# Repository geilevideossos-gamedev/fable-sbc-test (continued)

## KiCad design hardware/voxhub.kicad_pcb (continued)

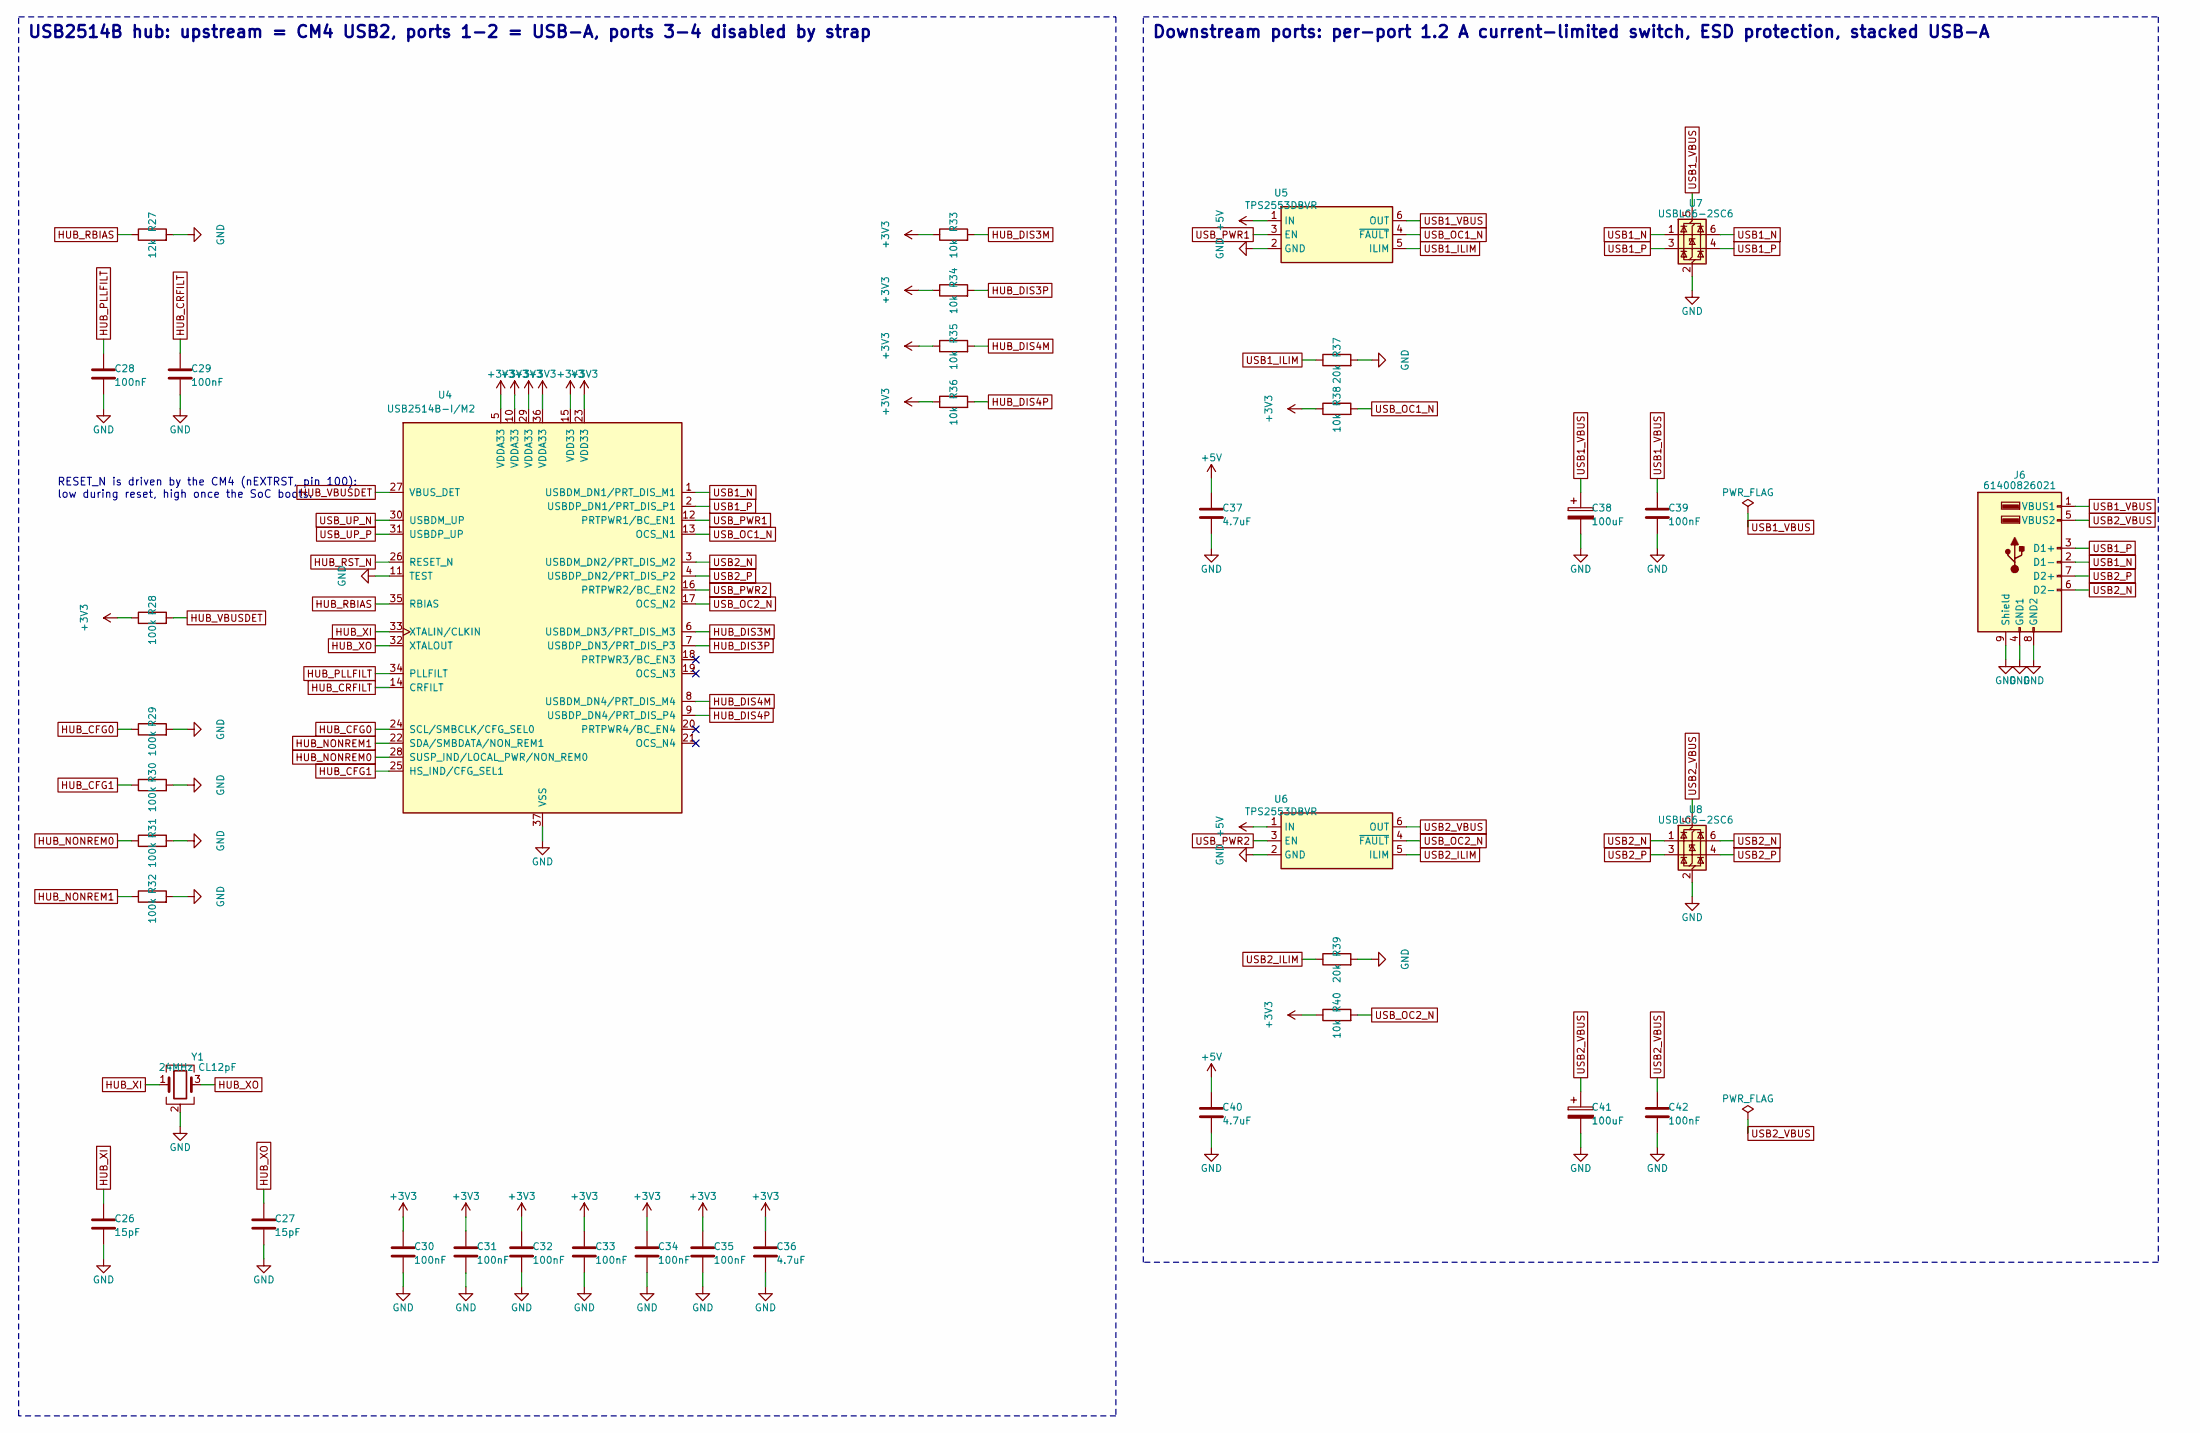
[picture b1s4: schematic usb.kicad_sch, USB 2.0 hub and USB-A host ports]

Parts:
C26, C27: 15pF; C_0402_1005Metric; MPN 0402CG150J500NT
C28, C29, C30, C31, C32, C33, C34, C35, C39, C42: 100nF; C_0402_1005Metric; MPN CL05B104KO5NNNC
C36, C37, C40: 4.7uF; C_0603_1608Metric; MPN CL10A475KA8NQNC
C38, C41: 100uF; CP_EIA-3528-21_Kemet-B; MPN T520B107M006ATE040
J6: 61400826021; USB_A_Wuerth_61400826021_Horizontal_Stacked; MPN 61400826021
R27: 12k; R_0402_1005Metric; MPN 0402WGF1202TCE
R28, R29, R30, R31, R32: 100k; R_0402_1005Metric; MPN 0402WGF1003TCE
R33, R34, R35, R36, R38, R40: 10k; R_0402_1005Metric; MPN 0402WGF1002TCE
R37, R39: 20k; R_0402_1005Metric; MPN 0402WGF2002TCE
U4: USB2514B-I/M2; QFN-36-1EP_6x6mm_P0.5mm_EP3.7x3.7mm; MPN USB2514B-I/M2
U5, U6: TPS2553DBVR; SOT-23-6; MPN TPS2553DBVR
U7, U8: USBLC6-2SC6; SOT-23-6; MPN USBLC6-2SC6
Y1: 24MHz CL12pF; Crystal_SMD_3225-4Pin_3.2x2.5mm; MPN X322524MOB4SI

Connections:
+3V3: C30.1, C31.1, C32.1, C33.1, C34.1, C35.1, C36.1, R28.1, R33.1, R34.1, R35.1, R36.1, R38.1, R40.1, U4.5 (VDDA33), U4.10 (VDDA33), U4.15 (VDD33), U4.23 (VDD33), U4.29 (VDDA33), U4.36 (VDDA33); also elsewhere on the board
+5V: C37.1, C40.1, U5.1 (IN), U6.1 (IN); also elsewhere on the board
GND: C26.2, C27.2, C28.2, C29.2, C30.2, C31.2, C32.2, C33.2, C34.2, C35.2, C36.2, C37.2, C38.2, C39.2, C40.2, C41.2, C42.2, J6.4 (GND1), J6.8 (GND2), J6.9 (Shield), R27.2, R29.2, R30.2, R31.2, R32.2, R37.2, R39.2, U4.11 (TEST), U4.37 (VSS), U5.2 (GND), U6.2 (GND), U7.2 (GND), U8.2 (GND), Y1.2 (G), Y1.4 (G); also elsewhere on the board
HUB_CFG0: R29.1, U4.24 (SCL/SMBCLK/CFG_SEL0)
HUB_CFG1: R30.1, U4.25 (HS_IND/CFG_SEL1)
HUB_CRFILT: C29.1, U4.14 (CRFILT)
HUB_DIS3M: R33.2, U4.6 (USBDM_DN3/PRT_DIS_M3)
HUB_DIS3P: R34.2, U4.7 (USBDP_DN3/PRT_DIS_P3)
HUB_DIS4M: R35.2, U4.8 (USBDM_DN4/PRT_DIS_M4)
HUB_DIS4P: R36.2, U4.9 (USBDP_DN4/PRT_DIS_P4)
HUB_NONREM0: R31.1, U4.28 (SUSP_IND/LOCAL_PWR/NON_REM0)
HUB_NONREM1: R32.1, U4.22 (SDA/SMBDATA/NON_REM1)
HUB_PLLFILT: C28.1, U4.34 (PLLFILT)
HUB_RBIAS: R27.1, U4.35 (RBIAS)
HUB_RST_N: U4.26 (RESET_N); also elsewhere on the board
HUB_VBUSDET: R28.2, U4.27 (VBUS_DET)
HUB_XI: C26.1, U4.33 (XTALIN/CLKIN), Y1.1
HUB_XO: C27.1, U4.32 (XTALOUT), Y1.3
USB1_ILIM: R37.1, U5.5 (ILIM)
USB1_N: J6.2 (D1-), U4.1 (USBDM_DN1/PRT_DIS_M1), U7.1 (I/O1), U7.6 (I/O1)
USB1_P: J6.3 (D1+), U4.2 (USBDP_DN1/PRT_DIS_P1), U7.3 (I/O2), U7.4 (I/O2)
USB1_VBUS: C38.1, C39.1, J6.1 (VBUS1), U5.6 (OUT), U7.5 (VBUS)
USB2_ILIM: R39.1, U6.5 (ILIM)
USB2_N: J6.6 (D2-), U4.3 (USBDM_DN2/PRT_DIS_M2), U8.1 (I/O1), U8.6 (I/O1)
USB2_P: J6.7 (D2+), U4.4 (USBDP_DN2/PRT_DIS_P2), U8.3 (I/O2), U8.4 (I/O2)
USB2_VBUS: C41.1, C42.1, J6.5 (VBUS2), U6.6 (OUT), U8.5 (VBUS)
USB_OC1_N: R38.2, U4.13 (OCS_N1), U5.4 (~FAULT)
USB_OC2_N: R40.2, U4.17 (OCS_N2), U6.4 (~FAULT)
USB_PWR1: U4.12 (PRTPWR1/BC_EN1), U5.3 (EN)
USB_PWR2: U4.16 (PRTPWR2/BC_EN2), U6.3 (EN)
USB_UP_N: U4.30 (USBDM_UP); also elsewhere on the board
USB_UP_P: U4.31 (USBDP_UP); also elsewhere on the board

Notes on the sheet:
USB2514B hub: upstream = CM4 USB2, ports 1-2 = USB-A, ports 3-4 disabled by strap
RESET_N is driven by the CM4 (nEXTRST, pin 100): low during reset, high once the SoC boots.
Downstream ports: per-port 1.2 A current-limited switch, ESD protection, stacked USB-A

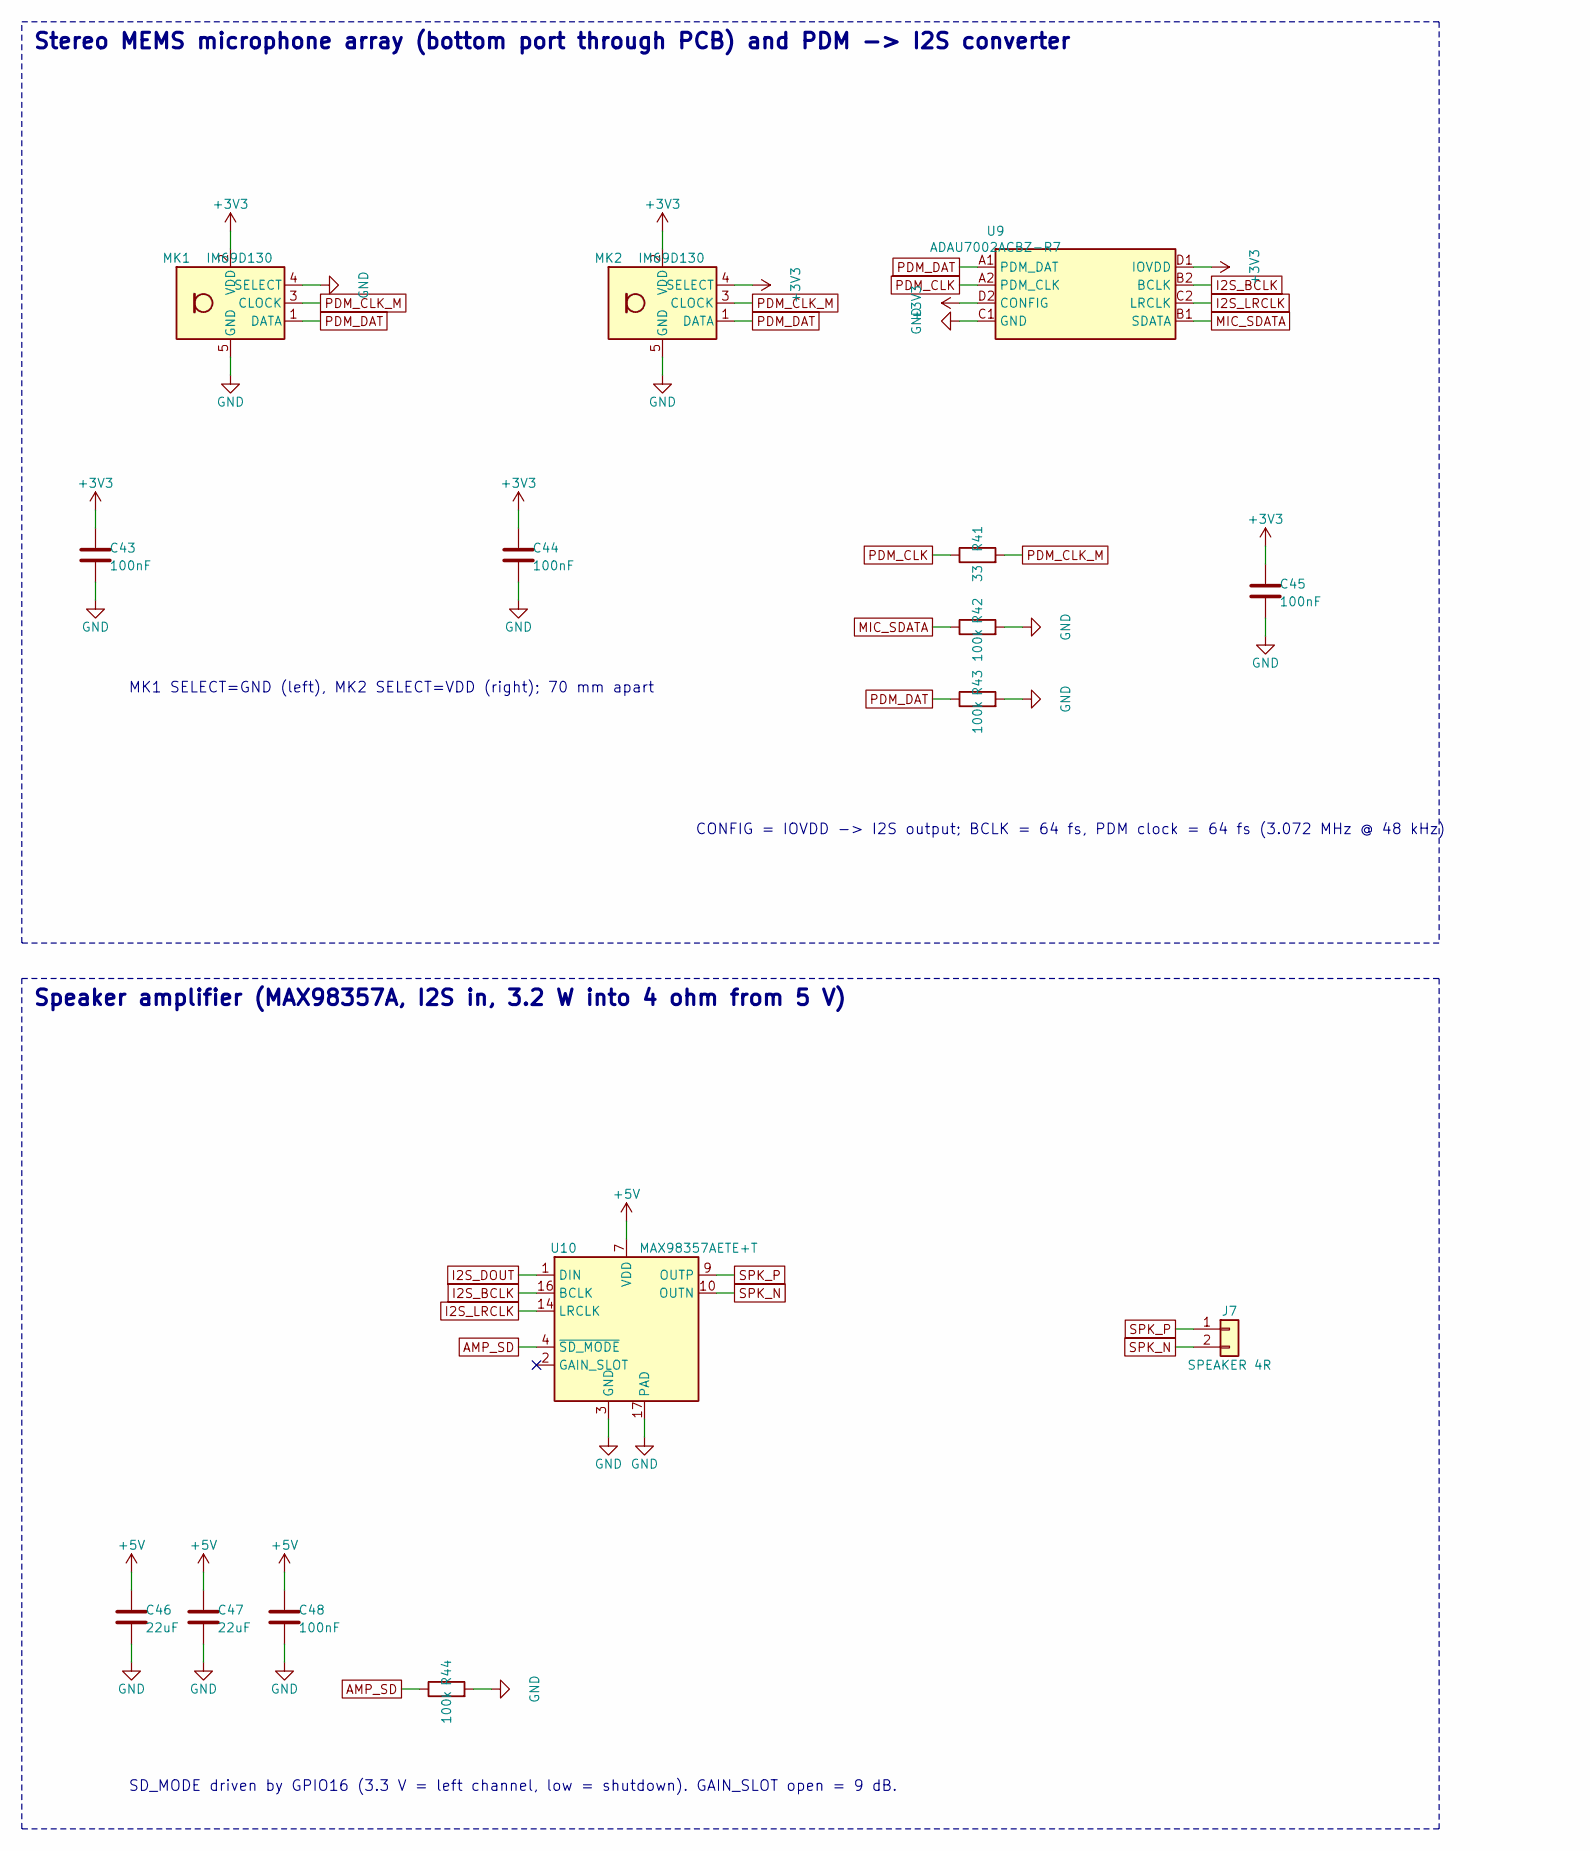
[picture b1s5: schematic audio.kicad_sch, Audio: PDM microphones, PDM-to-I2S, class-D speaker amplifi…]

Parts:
C43, C44, C45, C48: 100nF; C_0402_1005Metric; MPN CL05B104KO5NNNC
C46, C47: 22uF; C_1206_3216Metric; MPN CL31A226KAHNNNE
J7: SPEAKER 4R; JST_PH_B2B-PH-K_1x02_P2.00mm_Vertical; MPN B2B-PH-K-S(LF)(SN)
MK1, MK2: IM69D130; Infineon_PG-LLGA-5-1; MPN IM69D130V01XTSA1
R41: 33; R_0402_1005Metric; MPN 0402WGF330JTCE
R42, R43, R44: 100k; R_0402_1005Metric; MPN 0402WGF1003TCE
U9: ADAU7002ACBZ-R7; ADAU7002_WLCSP-8_0.76x1.56mm_P0.4mm; MPN ADAU7002ACBZ-R7
U10: MAX98357AETE+T; TQFN-16-1EP_3x3mm_P0.5mm_EP1.23x1.23mm; MPN MAX98357AETE+T

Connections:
+3V3: C43.1, C44.1, C45.1, MK1.2 (VDD), MK2.2 (VDD), MK2.4 (SELECT), U9.D1 (IOVDD), U9.D2 (CONFIG); also elsewhere on the board
+5V: C46.1, C47.1, C48.1, U10.7 (VDD), U10.8 (VDD); also elsewhere on the board
AMP_SD: R44.1, U10.4 (~SD_MODE); also elsewhere on the board
GND: C43.2, C44.2, C45.2, C46.2, C47.2, C48.2, MK1.4 (SELECT), MK1.5 (GND), MK2.5 (GND), R42.2, R43.2, R44.2, U9.C1 (GND), U10.3 (GND), U10.11 (GND), U10.15 (GND), U10.17 (PAD); also elsewhere on the board
I2S_BCLK: U9.B2 (BCLK), U10.16 (BCLK); also elsewhere on the board
I2S_DOUT: U10.1 (DIN); also elsewhere on the board
I2S_LRCLK: U9.C2 (LRCLK), U10.14 (LRCLK); also elsewhere on the board
MIC_SDATA: R42.1, U9.B1 (SDATA); also elsewhere on the board
PDM_CLK: R41.1, U9.A2 (PDM_CLK)
PDM_CLK_M: MK1.3 (CLOCK), MK2.3 (CLOCK), R41.2
PDM_DAT: MK1.1 (DATA), MK2.1 (DATA), R43.1, U9.A1 (PDM_DAT)
SPK_N: J7.2, U10.10 (OUTN)
SPK_P: J7.1, U10.9 (OUTP)

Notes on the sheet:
Stereo MEMS microphone array (bottom port through PCB) and PDM -> I2S converter
MK1 SELECT=GND (left), MK2 SELECT=VDD (right); 70 mm apart
CONFIG = IOVDD -> I2S output; BCLK = 64 fs, PDM clock = 64 fs (3.072 MHz @ 48 kHz)
Speaker amplifier (MAX98357A, I2S in, 3.2 W into 4 ohm from 5 V)
SD_MODE driven by GPIO16 (3.3 V = left channel, low = shutdown). GAIN_SLOT open = 9 dB.

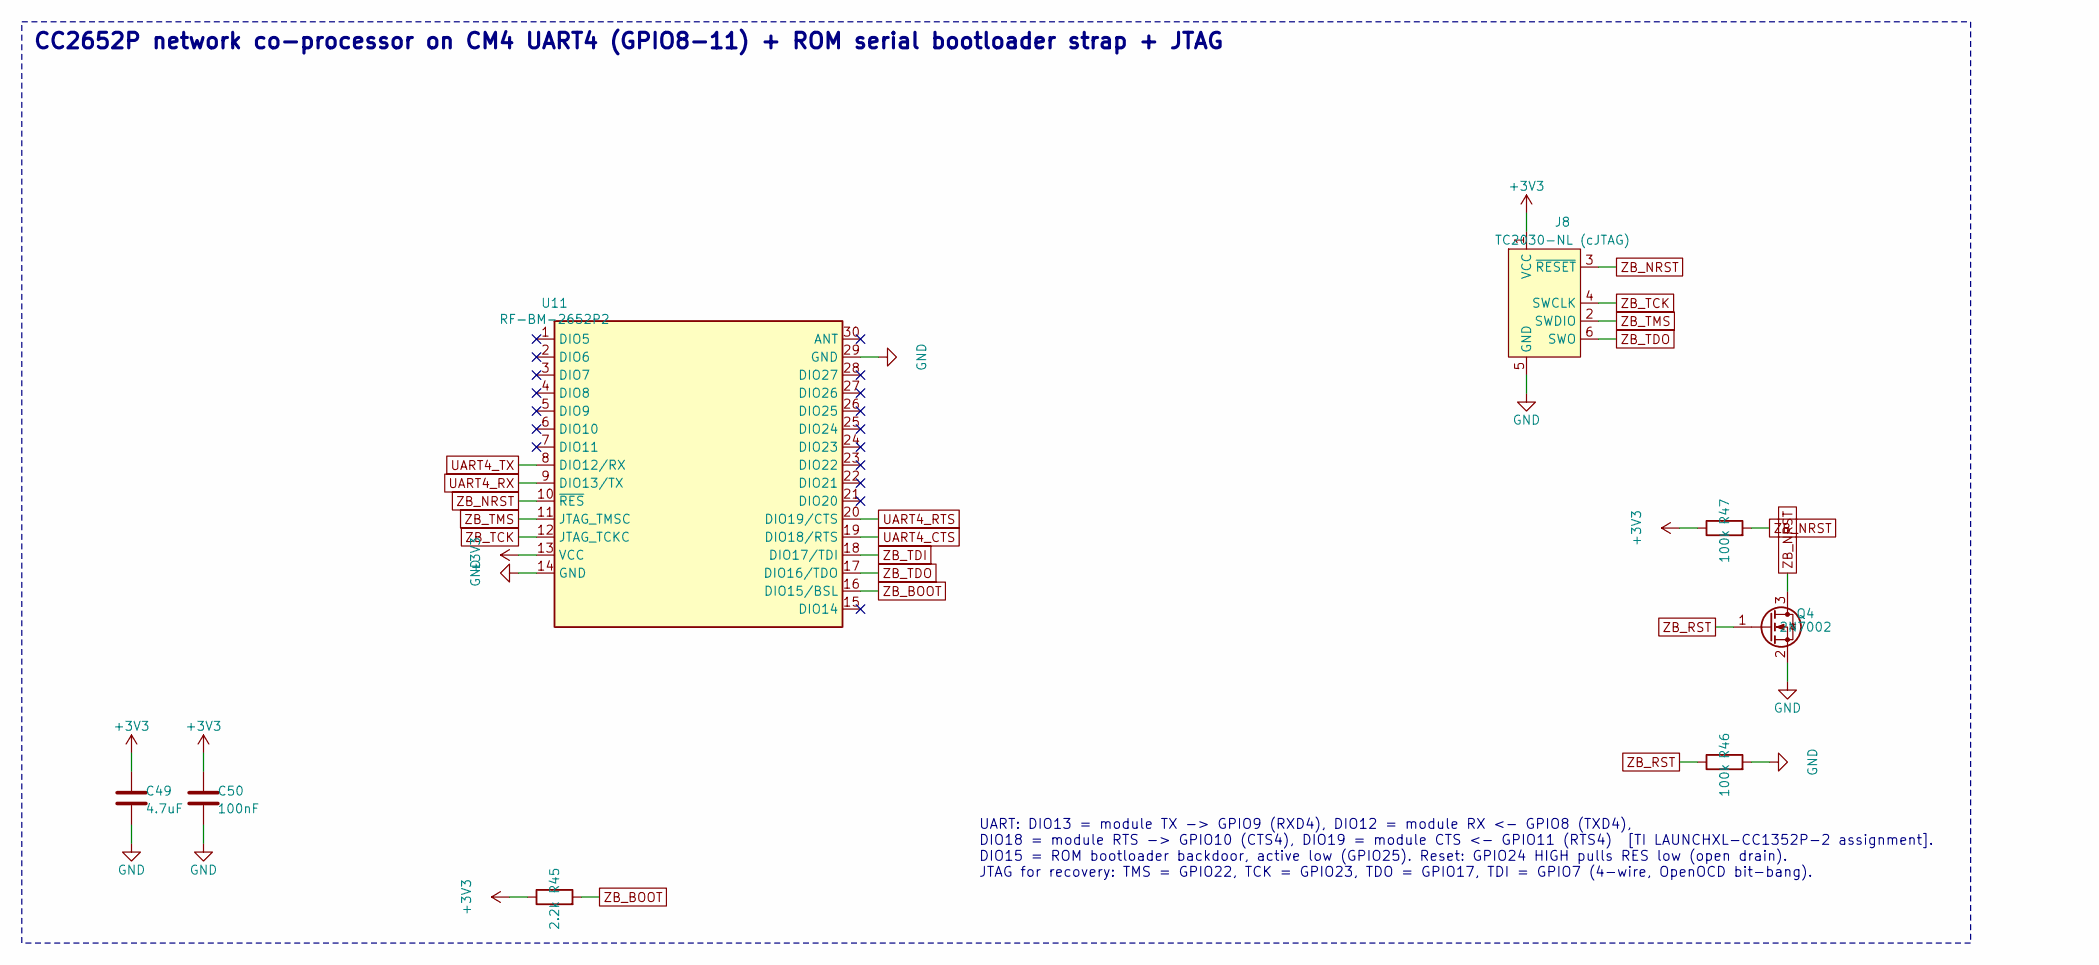
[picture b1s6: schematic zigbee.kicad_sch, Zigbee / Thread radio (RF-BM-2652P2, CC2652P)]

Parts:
C49: 4.7uF; C_0603_1608Metric; MPN CL10A475KA8NQNC
C50: 100nF; C_0402_1005Metric; MPN CL05B104KO5NNNC
J8: TC2030-NL (cJTAG); Tag-Connect_TC2030-IDC-NL_2x03_P1.27mm_Vertical; PartDescription Tag-Connect footprint (no part)
Q4: 2N7002; SOT-23; MPN 2N7002,215
R45: 2.2k; R_0402_1005Metric; MPN 0402WGF2201TCE
R46, R47: 100k; R_0402_1005Metric; MPN 0402WGF1003TCE
U11: RF-BM-2652P2; RFstar_RF-BM-2652P2; MPN RF-BM-2652P2

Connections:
+3V3: C49.1, C50.1, J8.1 (VCC), R45.1, R47.1, U11.13 (VCC); also elsewhere on the board
GND: C49.2, C50.2, J8.5 (GND), Q4.2 (S), R46.2, U11.14 (GND), U11.29 (GND); also elsewhere on the board
UART4_CTS: U11.19 (DIO18/RTS); also elsewhere on the board
UART4_RTS: U11.20 (DIO19/CTS); also elsewhere on the board
UART4_RX: U11.9 (DIO13/TX); also elsewhere on the board
UART4_TX: U11.8 (DIO12/RX); also elsewhere on the board
ZB_BOOT: R45.2, U11.16 (DIO15/BSL); also elsewhere on the board
ZB_NRST: J8.3 (~RESET), Q4.3 (D), R47.2, U11.10 (~RES)
ZB_RST: Q4.1 (G), R46.1; also elsewhere on the board
ZB_TCK: J8.4 (SWCLK), U11.12 (JTAG_TCKC); also elsewhere on the board
ZB_TDI: U11.18 (DIO17/TDI); also elsewhere on the board
ZB_TDO: J8.6 (SWO), U11.17 (DIO16/TDO); also elsewhere on the board
ZB_TMS: J8.2 (SWDIO), U11.11 (JTAG_TMSC); also elsewhere on the board

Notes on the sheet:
CC2652P network co-processor on CM4 UART4 (GPIO8-11) + ROM serial bootloader strap + JTAG
UART: DIO13 = module TX -> GPIO9 (RXD4), DIO12 = module RX <- GPIO8 (TXD4), DIO18 = module RTS -> GPIO10 (CTS4), DIO19 = module CTS <- GPIO11 (RTS4) [TI LAUNCHXL-CC1352P-2 assignment]. DIO15 = ROM bootloader backdoor, active low (GPIO25). Reset: GPIO24 HIGH pulls RES low (open drain). JTAG for reco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

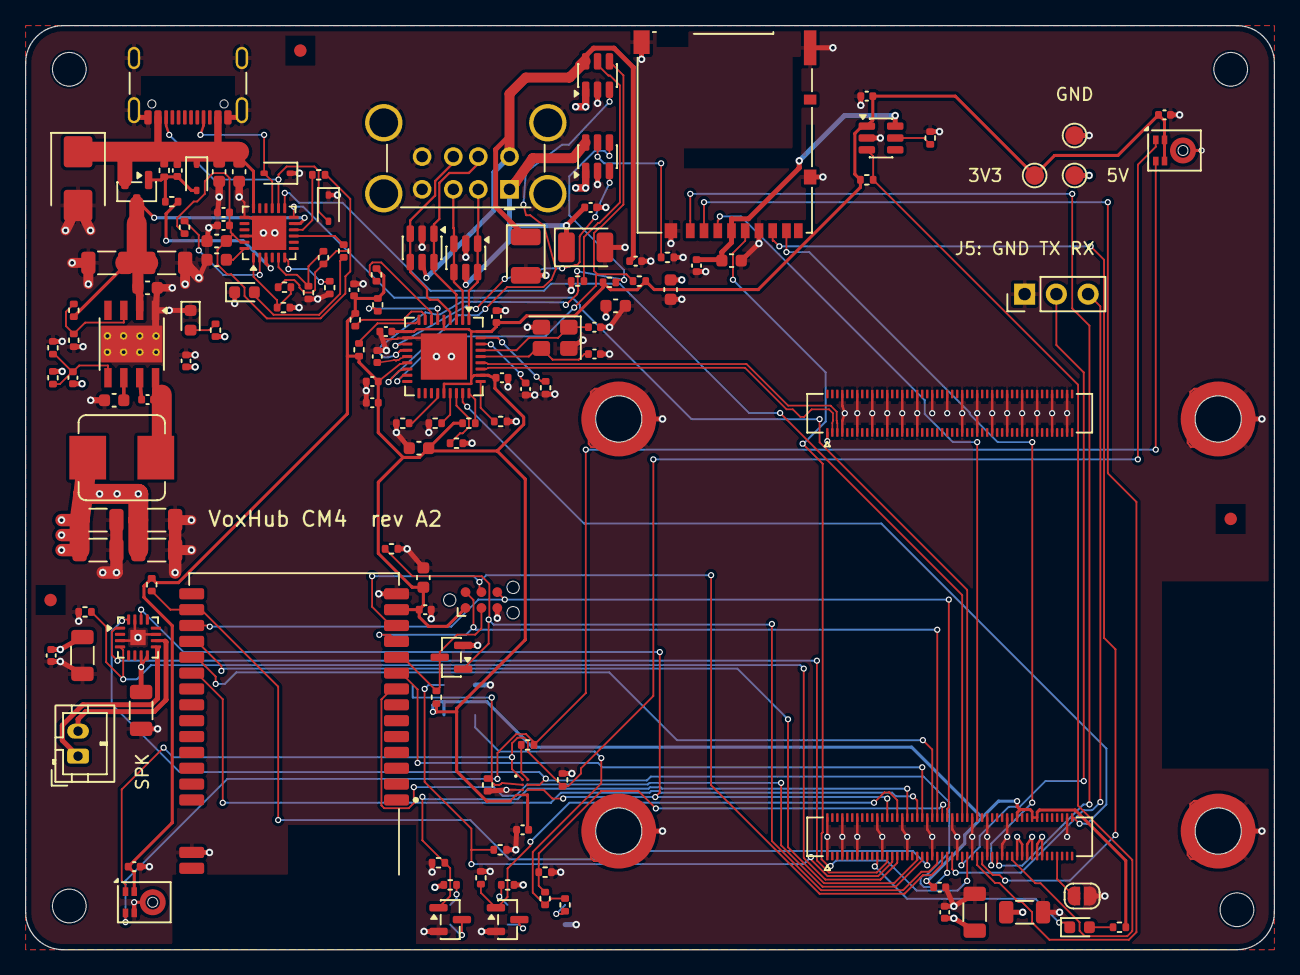
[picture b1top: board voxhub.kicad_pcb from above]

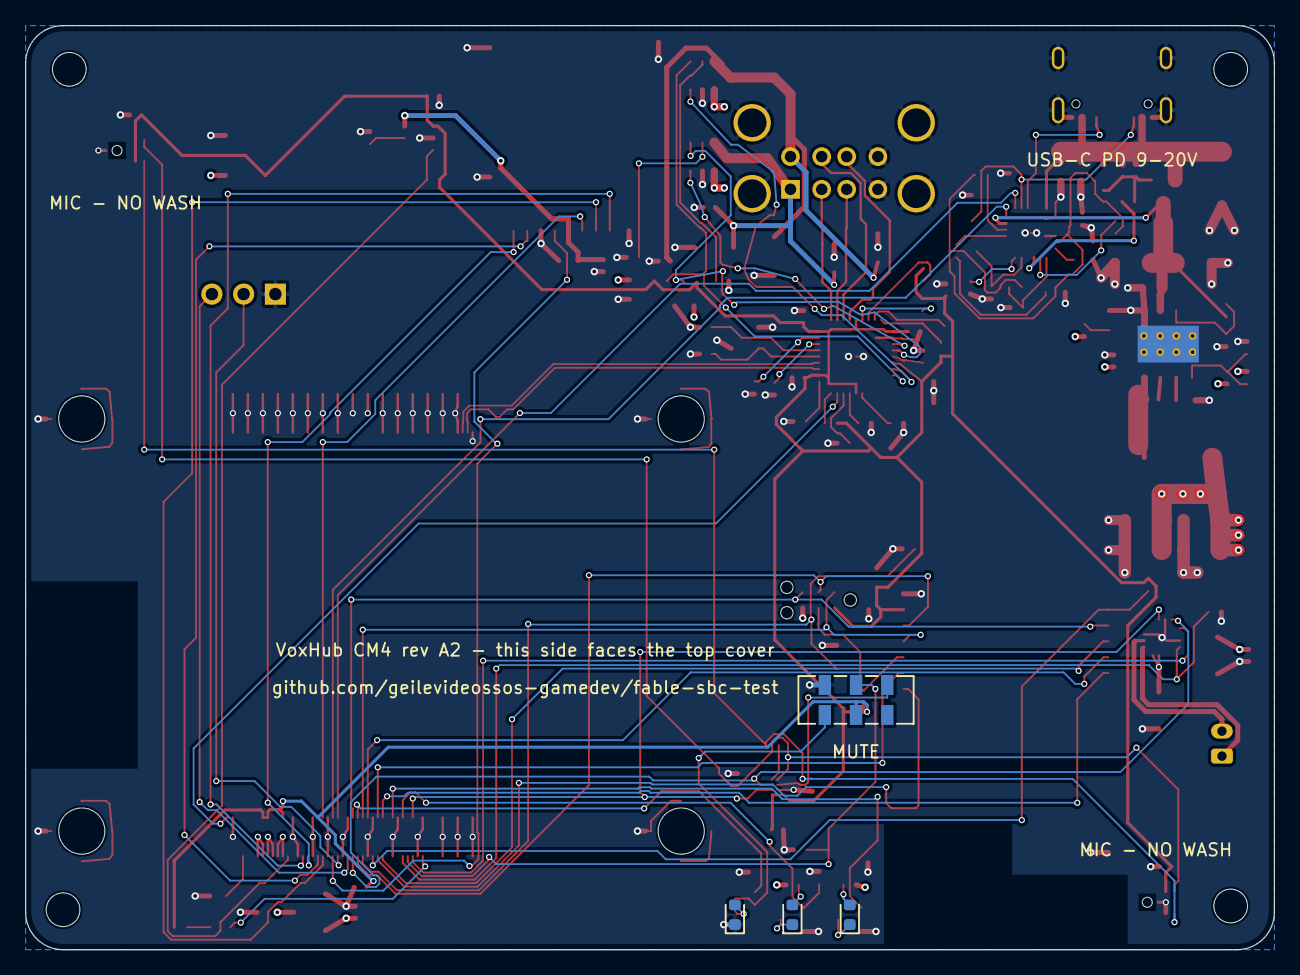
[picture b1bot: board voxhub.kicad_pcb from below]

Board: 4 copper layers, 100.0 x 74.0 mm, 150 parts (4 on the bottom side), 100 nets.

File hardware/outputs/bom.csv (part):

Item,Qty,References,Value,Description,Footprint,Manufacturer,MPN,DNP,LCSC Part #,JLCPCB type,JLCPCB stock,LCSC stock,JLCPCB USD @1,JLCPCB USD @10,JLCPCB USD @100,Ext. USD @1,Ext. USD @100,Assembly,DigiKey MPN (second source),DigiKey PN,DigiKey status,DigiKey stock,DigiKey USD @1,DigiKey USD @100,Other second sources,"Sourcing note (JLCPCB/LCSC checked 2026-11-12, DigiKey 2026-11-11)"
1,1,C1,1uF,CAP CER 1uF 50V X5R 0603,C_0603_1608Metric,Samsung Electro-Mechanics,CL10A105KB8NNNC,,C15849,Basic,13930106,1382400,0.0113,0.0113,0.0113,0.01,0.01,SMT,C1608X5R1H105K080AB,445-7468-1-ND,Active,9276,0.17,0.0579,TDK C1608X5R1H105K080AB (the A1 part),same ratings as the A1 part (50 V X5R)
2,1,C2,100nF,CAP CER 100nF 50V X7R 0603,C_0603_1608Metric,Yageo,CC0603KRX7R9BB104,,C14663,Basic,36401649,249700,0.006,0.006,0.006,0.01,0.01,SMT,C0603C104K5RACTU,399-C0603C104K5RACTUCT-ND,Active,2463252,0.14,0.046,KEMET C0603C104K5RACTU (the A1 part); any 0603 100 nF X7R 50 V,same ratings as the A1 part
3,3,C3 C5 C11,1uF,CAP CER 1uF 25V X7R 0603,C_0603_1608Metric,Samsung Electro-Mechanics,CL10B105KA8NNNC,,C29936,Extended,4509875,4284100,0.0124,0.0124,0.0097,0.04,0.03,SMT,C1608X7R1C105K080AC,445-1604-1-ND,Active,805635,0.12,0.0411,"TDK C1608X7R1C105K080AC (16 V, the A1 part), Samsung CL10B105KO8NNNC (16 V, JLCPCB C59782): 1 uF X7R 0603",25 V instead of 16 V; X7R kept on purpose (DC bias)
4,23,C4 C6 C12 C18 C19 C21 C24 C25 C28 C29 C30 C31 C32 C33 C34 C35 C39 C42 C43 C44 C45 C48 C50,100nF,CAP CER 100nF 16V X7R 0402,C_0402_1005Metric,Samsung Electro-Mechanics,CL05B104KO5NNNC,,C1525,Basic,33093790,3017800,0.0029,0.0029,0.0029,0.07,0.07,SMT,CL05B104KO5NNNC,1276-1001-1-ND,Active,10000,0.10,0.0115,any 0402 100 nF X7R >= 16 V,
5,1,C7,10nF,CAP CER 10nF 50V X7R 0402,C_0402_1005Metric,Samsung Electro-Mechanics,CL05B103KB5NNNC,,C15195,Basic,5543060,1498700,0.0037,0.0037,0.0037,0.00,0.00,SMT,CL05B103KB5NNNC,1276-1028-1-ND,Active,3769991,0.10,0.0104,any 0402 10 nF X7R 50 V,
6,2,C8 C9,10uF,CAP CER 10uF 50V X7R 1206,C_1206_3216Metric,Samsung Electro-Mechanics,CL31B106KBHNNNE,,C89632,Extended,468888,319710,0.2124,0.2124,0.1646,0.42,0.33,SMT,CL31B106KBHNNNE,1276-6767-1-ND,Active,0,0.42,0.168,TDK C3216X7R1H106KT0A0E (JLCPCB C694197),X7R as the LMR33640 data sheet requires for CIN. A1 flagged this line: 0 at DigiKey. JLCPCB has it in stock
7,1,C10,220nF,CAP CER 220nF 50V X7R 0603,C_0603_1608Metric,Murata,GRM188R71H224KAC4D,,C669503,Extended,4047,4040,0.0738,0.0738,0.0609,0.07,0.06,SMT,GRM188R71H224KAC4D,490-12546-1-ND,Active,not shown,0.15,0.052,"Samsung CL10B224KB8NNNC (JLCPCB C64705), Yageo CC0603KRX7R9BB224 (C107083): 220 nF 50 V X7R 0603",LMR33640 input bypass must be 220 nF / 50 V / X7R (data sheet)
8,1,C13,22pF,CAP CER 22pF 50V C0G 0402,C_0402_1005Metric,FH (Guangdong Fenghua),0402CG220J500NT,DNP,C1555,Basic,1490772,243900,0.0019,0.0019,0.0019,0.00,0.00,SMT,CL05C220JB5NNNC,1276-1116-1-ND,Active,372620,0.10,0.0212,any 0402 22 pF C0G 50 V,DNP
9,8,C14 C15 C16 C17 C22 C23 C46 C47,22uF,CAP CER 22uF 25V X5R 1206,C_1206_3216Metric,Samsung Electro-Mechanics,CL31A226KAHNNNE,,C12891,Basic,2517345,967820,0.1028,0.1028,0.1028,0.82,0.82,SMT,CL31A226KOHNNNE,1276-3048-1-ND,Active,0,0.44,0.1757,"Samsung CL31A226KOHNNNE (16 V, the A1 part, JLCPCB C90146)","25 V instead of 16 V, same case height (1.6 mm)"
10,5,C20 C36 C37 C40 C49,4.7uF,CAP CER 4.7uF 25V X5R 0603,C_0603_1608Metric,Samsung Electro-Mechanics,CL10A475KA8NQNC,,C69335,Extended,744008,548530,0.0427,0.0427,0.0311,0.21,0.16,SMT,C1608X5R1E475K080AC,445-9050-1-ND,Active,472029,0.25,0.0914,TDK C1608X5R1E475K080AC (the A1 part),same ratings as the A1 part (25 V X5R)
11,2,C26 C27,15pF,CAP CER 15pF 50V C0G 0402,C_0402_1005Metric,FH (Guangdong Fenghua),0402CG150J500NT,,C1548,Basic,1091876,423300,0.0026,0.0026,0.0026,0.01,0.01,SMT,,,not carried / not looked up,,,,any 0402 15 pF C0G 50 V,crystal load capacitors for CL 12 pF
12,2,C38 C41,100uF,CAP POLYMER TANT 100uF 6.3V 40mOhm 3528,CP_EIA-3528-21_Kemet-B,KEMET,T520B107M006ATE040,,C116740,Extended,2609,2609,0.5578,0.4548,0.355,1.12,0.71,SMT,T520B107M006ATE070,399-4009-1-ND,Active,19364,0.98,0.4391,"KEMET T520B107M006ATE070 (the A1 part, 70 mOhm), Vishay T55B107M6R3C0040 (JLCPCB C2158743): same footprint","replaces the 70 mOhm version: 40 mOhm, 1.8 A ripple, same case and ratings"
13,1,D1,SMBJ22A,TVS 22V 600W unidirectional SMB,D_SMB,Littelfuse,SMBJ22A,,C224015,Extended,1918,1915,0.1262,0.1262,0.1026,0.13,0.10,SMT,SMBJ22A,SMBJ22ALFCT-ND,Active,3431,0.50,0.1959,SMBJ22A from Bourns / Diodes / ST / Taiwan Semi: drop-in,LCSC C224015 is the Littelfuse listing
14,2,D2 D3,SD24C,ESD diode 24V bidirectional SOD-323,D_SOD-323,Littelfuse,SD24C-01FTG,,C207246,Extended,8806,8805,0.204,0.204,0.159,0.41,0.32,SMT,SD24C-01FTG,F6446CT-ND,Active,219,0.66,0.2598,no equal-or-better SOD-323 part found,LCSC C207246 is the Littelfuse listing
15,2,D4 D9,PD FAULT (red),"LED red 631nm 0603, 30mA",LED_0603_1608Metric,Lite-On,LTST-C191KRKT,,C125099,Extended,380670,377740,0.0192,0.0192,0.0192,0.04,0.04,SMT,150060RS75000,732-4978-1-ND,Active,269986,0.15,0.1239,Wurth 150060RS75000 (the A1 part); Hubei KENTO KT-0603R is JLCPCB Basic but rated 25 mA / 40 mW,30 mA / 75 mW / -55..+85 C: every rating of the A1 part met
16,1,D5,10V,Zener 10V 300mW SOD-323,D_SOD-323,onsemi,MM3Z10VT1G,,C39057,Extended,21866,21860,0.04,0.04,0.04,0.04,0.04,SMT,SZMM3Z10VT1G,SZMM3Z10VT1GOSCT-ND,Active,17291,0.29,0.1092,"onsemi SZMM3Z10VT1G (same die with AEC-Q101, JLCPCB C894520 - no footprint record in the JLCPCB library) or any 10 V SOD-323 zener >= 300 mW",
17,2,D6 D10,PWR (green),"LED green 570nm 0603, 30mA",LED_0603_1608Metric,Wurth Elektronik,150060VS75000,,C6848499,Extended,29587,,0.2043,0.2043,0.163,0.41,0.33,SMT,150060VS75000,732-4980-1-ND,Active,494853,0.15,0.1239,"any 0603 AlInGaP green LED, VF about 2.0 V",
18,1,D7,GREEN,"LED green 520nm 0603, 30mA (status, side B)",LED_0603_1608Metric,Hubei KENTO,KT-0603G,,C12624,Extended,292541,289550,0.0119,0.0119,0.0119,0.01,0.01,SMT,,,not carried / not looked up,,,,"any 0603 InGaN green LED >= 25 mA, -40..+85 C (VF about 2.7 V at 2 mA)",replaces the reverse-mount Wurth 156120GS75000 (0 at JLCPCB): ordinary LED on side B inside the light pipe
19,1,D8,BLUE,"LED blue 468nm 0603, 30mA (status, side B)",LED_0603_1608Metric,Hubei KENTO,KT-0603B,,C2288,Extended,82388,72150,0.0106,0.0106,0.0106,0.01,0.01,SMT,,,not carried / not looked up,,,,"any 0603 InGaN blue LED >= 25 mA, -40..+85 C",replaces the reverse-mount Wurth 156120BS75000 (not at JLCPCB): ordinary LED on side B inside the light pipe
20,4,H5 H6 H7 H8,CM4 spacer M2.5x1.5,"SMT spacer M2.5 internal thread, 1.5mm",Mounting_Wuerth_WA-SMSI-M2.5_H1.5mm_9774015151,Wurth Elektronik,9774015151R,,C5353804,Extended,230,,0.5611,0.5251,0.5251,2.24,2.10,SMT,9774015151R,732-7068-1-ND,Active,109674,1.16,0.895,Sinhoo SMTSO2515CTJ (JLCPCB C2915629) needs a 4.25 mm hole and a 6.3 mm pad - not a drop-in,"230 at JLCPCB, not sold at LCSC"
21,1,J1,USB4105-GF-A,"USB-C receptacle 16-pin USB 2.0, top mount",USB_C_Receptacle_GCT_USB4105-xx-A_16P_TopMnt_Horizontal,GCT,USB4105-GF-A,,C3020560,Extended,17519,14825,1.0207,0.8277,0.6363,1.02,0.64,SMT,USB4105-GF-A,2073-USB4105-GF-ACT-ND,Active,263569,0.80,0.5745,"none verified (GCT USB4105-GF-A-120: same footprint, longer shell stakes)",
22,2,J2 J3,DF40C-100DS-0.4V(51),CONN mezzanine 100pos 0.4mm receptacle (CM4 socket),CM4_J1_DF40C-100DS,Hirose,DF40C-100DS-0.4V(51),,C597931,Extended,1052,0,0.9667,0.8277,0.6494,1.93,1.30,SMT,DF40C-100DS-0.4V(51),H11615CT-ND,Active,164626,2.39,1.7271,"Hirose DF40HC(3.0)-100DS-0.4V(51): same land pattern, 3.0 mm stack (needs 3 mm spacers)",
23,1,J4,DM3AT-SF-PEJM5,microSD push-push socket,microSD_HC_Hirose_DM3AT-SF-PEJM5,Hirose,DM3AT-SF-PEJM5,,C114218,Extended,14909,14422,1.3903,1.1646,0.8996,1.39,0.90,SMT,DM3AT-SF-PEJM5,HR1964CT-ND,Active,74836,3.55,2.5656,none drop-in (Molex 104031-0811 needs a new footprint),
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
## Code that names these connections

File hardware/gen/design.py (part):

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CM4_NAMES = """1:GND 2:GND 3:Ethernet_Pair3_P 4:Ethernet_Pair1_P 5:Ethernet_Pair3_N 6:Ethernet_Pair1_N 7:GND 8:GND
9:Ethernet_Pair2_N 10:Ethernet_Pair0_N 11:Ethernet_Pair2_P 12:Ethernet_Pair0_P 13:GND 14:GND 15:Ethernet_nLED3
16:Ethernet_SYNC_IN 17:Ethernet_nLED2 18:Ethernet_SYNC_OUT 19:Ethernet_nLED1 20:EEPROM_nWP 21:Pi_nLED_Activity
22:GND 23:GND 24:GPIO26 25:GPIO21 26:GPIO19 27:GPIO20 28:GPIO13 29:GPIO16 30:GPIO6 31:GPIO12 32:GND 33:GND 34:GPIO5
35:ID_SC 36:ID_SD 37:GPIO7 38:GPIO11 39:GPIO8 40:GPIO9 41:GPIO25 42:GND 43:GND 44:GPIO10 45:GPIO24 46:GPIO22
47:GPIO23 48:GPIO27 49:GPIO18 50:GPIO17 51:GPIO15 52:GND 53:GND 54:GPIO4 55:GPIO14 56:GPIO3 57:SD_CLK 58:GPIO2
59:GND 60:GND 61:SD_DAT3 62:SD_CMD 63:SD_DAT0 64:SD_DAT5 65:GND 66:GND 67:SD_DAT1 68:SD_DAT4 69:SD_DAT2 70:SD_DAT7
71:GND 72:SD_DAT6 73:SD_VDD_Override 74:GND 75:SD_PWR_ON 76:Reserved 77:+5V 78:GPIO_VREF 79:+5V 80:SCL0 81:+5V
82:SDA0 83:+5V 84:+3.3V_OUT 85:+5V 86:+3.3V_OUT 87:+5V 88:+1.8V_OUT 89:WL_nDisable 90:+1.8V_OUT 91:BT_nDisable
92:RUN_PG 93:nRPIBOOT 94:AnalogIP0 95:nPWR_LED 96:AnalogIP1 97:Camera_GPIO 98:GND 99:GLOBAL_EN 100:nEXTRST
101:USB_OTG_ID 102:PCIe_CLK_nREQ 103:USB2_N 104:Reserved 105:USB2_P 106:Reserved 107:GND 108:GND 109:PCIe_nRST
110:PCIe_CLK_P 111:VDAC_COMP 112:PCIe_CLK_N 113:GND 114:GND 115:CAM1_D0_N 116:PCIe_RX_P 117:CAM1_D0_P 118:PCIe_RX_N
119:GND 120:GND 121:CAM1_D1_N 122:PCIe_TX_P 123:CAM1_D1_P 124:PCIe_TX_N 125:GND 126:GND 127:CAM1_C_N 128:CAM0_D0_N
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    res(s, rled, x, 135, V5, "LED%d_A" % i)
    led(s, key, x + 20, 150, "LED%d_A" % i, "LED%d_K" % i, name, pos=(34.0 + i * 4.6, 71.2, 90, "B"))
    q = ref("Q"); s.place("2N7002", q, "2N7002", x + 5, 180, {"1": en, "2": GND, "3": "LED%d_K" % i}, footprint=PARTS["Q_N"][3], fields=F("Q_N"))
    res(s, "10k", x, 200, en, GND)   # beats the SoC's ~50k boot-time pull-up on GPIO5/6
s.place("SW_DPDT_x2", "SW1", "JS202011JCQN (MUTE)", 375, 140, {"1": "NC", "2": V33, "3": "MIC_MUTE"}, unit=1, footprint=PARTS["SW_MUTE"][3], fields=F("SW_MUTE"))
s.place("SW_DPDT_x2", "SW1", "JS202011JCQN (MUTE)", 375, 165, {"4": "MIC_SDATA", "5": "I2S_DIN", "6": GND}, unit=2, footprint=PARTS["SW_MUTE"][3], fields=F("SW_MUTE"))
res(s, "150", 370, 185, "MIC_MUTE", "MUTE_LED_A"); led(s, "LED_R", 395, 200, "MUTE_LED_A", GND, "RED (muted)", pos=(43.2, 71.2, 90, "B"))
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         "14": "I2S_LRCLK", "15": GND, "16": "I2S_BCLK", "17": GND}, fields=F("U_AMP"))
cap(s, "C_22u", 30, 245, V5); cap(s, "C_22u", 41, 245, V5); cap(s, "C_100n", 52, 245, V5); res(s, "100k", 75, 255, "AMP_SD", GND)
s.place("Conn_01x02", "J7", "SPEAKER 4R", 185, 205, {"1": "SPK_P", "2": "SPK_N"}, footprint=PARTS["J_SPK"][3], fields=F("J_SPK"))
s.text("SD_MODE driven by GPIO16 (3.3 V = left channel, low = shutdown). GAIN_SLOT open = 9 dB.", 30, 270, size=1.5)

# =========================================================================
# Sheet 6: Zigbee / Thread radio
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z = {n: "NC" for n in range(1, 31)}
z.update({13: V33, 14: GND, 29: GND, 8: "UART4_TX", 9: "UART4_RX", 19: "UART4_CTS", 20: "UART4_RTS", 10: "ZB_NRST", 16: "ZB_BOOT",
          11: "ZB_TMS", 12: "ZB_TCK", 17: "ZB_TDO", 18: "ZB_TDI"})
s.box(15, 20, 290, 150, "CC2652P network co-processor on CM4 UART4 (GPIO8-11) + ROM serial bootloader strap + JTAG")
s.place("RF-BM-2652P2", "U11", "RF-BM-2652P2", 110, 85, {str(k): v for k, v in z.items()}, fields=F("U_ZB"))
cap(s, "C_4u7", 30, 130, V33); cap(s, "C_100n", 41, 130, V33)
res(s, "2.2k", 90, 143, V33, "ZB_BOOT")
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s.place("Conn_ARM_SWD_TagConnect_TC2030-NL", "J8", "TC2030-NL (cJTAG)", 230, 60,
        {"1": V33, "2": "ZB_TMS", "3": "ZB_NRST", "4": "ZB_TCK", "5": GND, "6": "ZB_TDO"}, in_bom=False,
        fields={"MPN": "", "Manufacturer": "", "PartDescription": "Tag-Connect footprint (no part)"})
s.text("UART: DIO13 = module TX -> GPIO9 (RXD4), DIO12 = module RX <- GPIO8 (TXD4),\nDIO18 = module RTS -> GPIO10 (CTS4), DIO19 = module CTS <- GPIO11 (RTS4)  [TI LAUNCHXL-CC1352P-2 assignment].\n"
       "DIO15 = ROM bootloader backdoor, active low (GPIO25). Reset: GPIO24 HIGH pulls RES low (open drain).\n"
       "JTAG for recovery: TMS = GPIO22, TCK = GPIO23, TDO = GPIO17, TDI = GPIO7 (4-wire, OpenOCD bit-bang).", 150, 141, size=1.4)

# =========================================================================
# Root sheet: mechanical items
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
